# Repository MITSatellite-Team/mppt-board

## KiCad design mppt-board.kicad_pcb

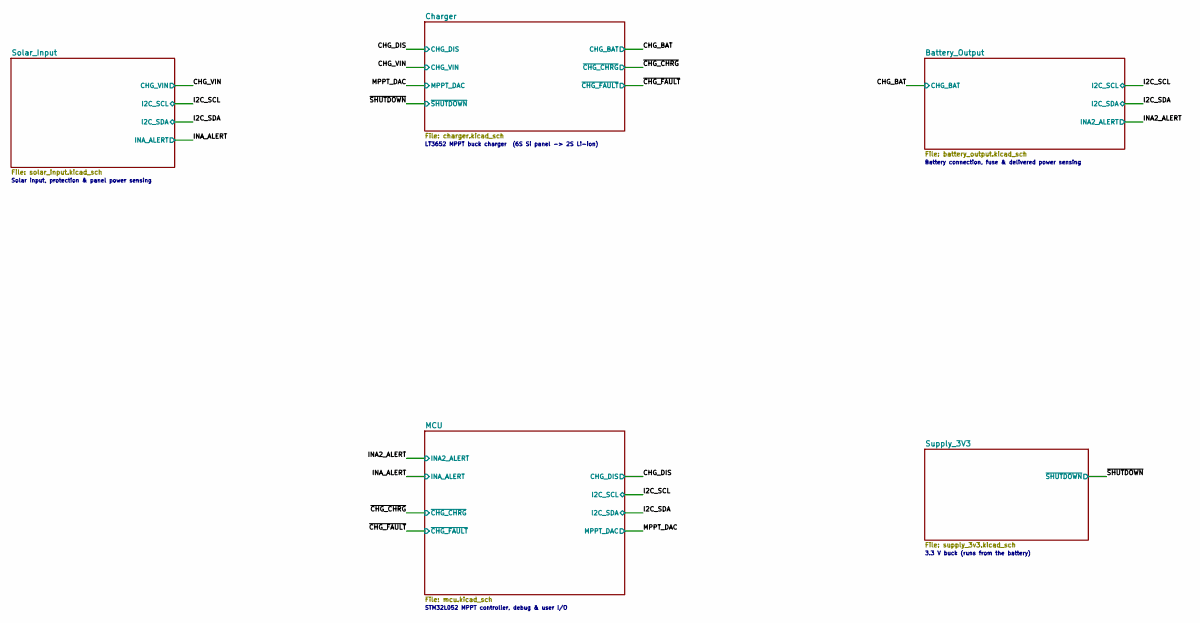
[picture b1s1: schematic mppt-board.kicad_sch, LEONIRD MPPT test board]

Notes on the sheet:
3.3 V buck (runs from the battery)
Solar input, protection & panel power sensing
STM32L052 MPPT controller, debug & user I/O
Battery connection, fuse & delivered power sensing
LT3652 MPPT buck charger (6S Si panel -> 2S Li-ion)

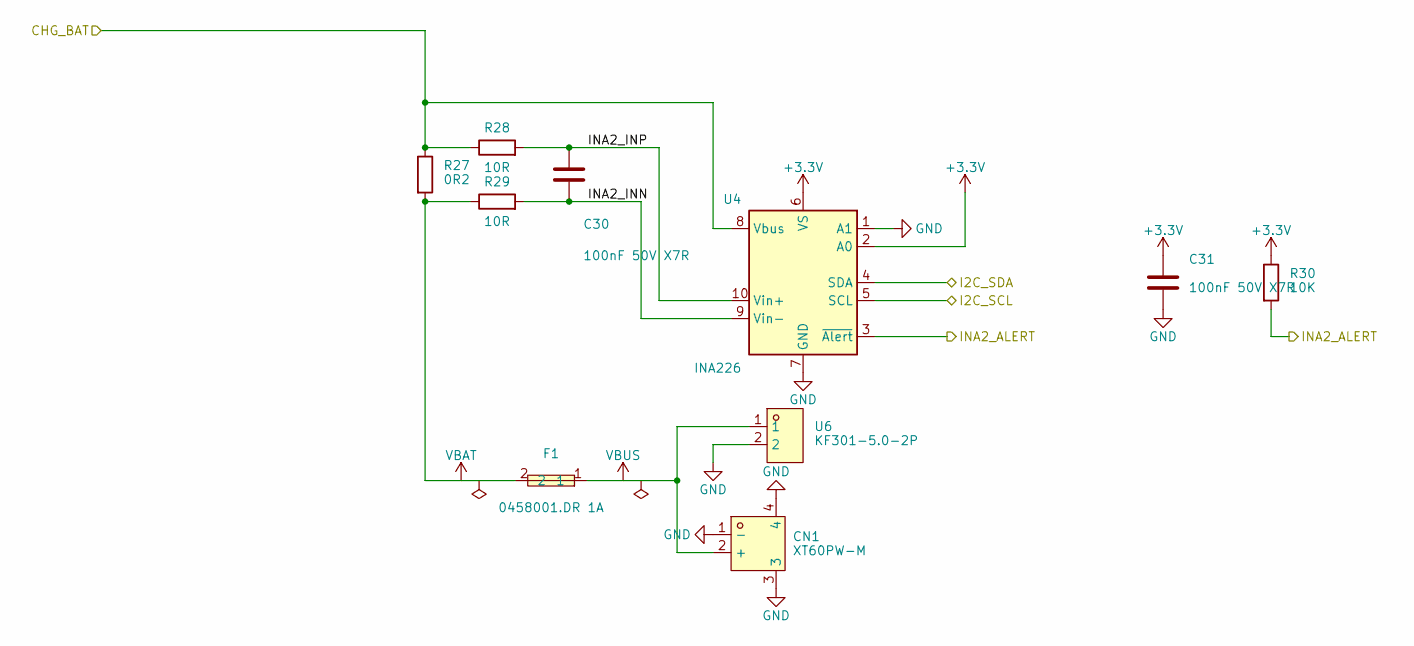
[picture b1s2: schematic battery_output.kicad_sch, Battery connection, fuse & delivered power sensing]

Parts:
C30, C31: 100nF 50V X7R; C_0603_1608Metric; MPN CC0603KRX7R9BB104; LCSC Part C14663
CN1: XT60PW-M; CONN-TH_XT60PW-M; MPN XT60PW-M; LCSC Part C98732
F1: 0458001.DR 1A; Fuse_1206_3216Metric; MPN 0458001.DR; LCSC Part C187559
R27: 0R2; R_1206_3216Metric; MPN RL12FTNR200; LCSC Part C160920
R28, R29: 10R; R_0603_1608Metric; MPN 0603WAF100JT5E; LCSC Part C22859
R30: 10K; R_0603_1608Metric; MPN 0603WAF1002T5E; LCSC Part C25804
U4: INA226; TSSOP-10_3x3mm_P0.5mm; MPN INA226AIDGSR; LCSC Part C49851
U6: KF301-5.0-2P; CONN-TH_P5.00_KF301-5.0-2P; MPN KF301-5.0-2P; LCSC Part C474881

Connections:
+3.3V: C31.1, R30.1, U4.2 (A0), U4.6 (VS); also elsewhere on the board
/Battery_Output/INA2_INN: C30.2, R29.2, U4.9 (Vin-)
/Battery_Output/INA2_INP: C30.1, R28.2, U4.10 (Vin+)
/CHG_BAT: R27.1, R28.1, U4.8 (Vbus); also elsewhere on the board
/I2C_SCL: U4.5 (SCL); also elsewhere on the board
/I2C_SDA: U4.4 (SDA); also elsewhere on the board
/INA2_ALERT: R30.2, U4.3 (~Alert); also elsewhere on the board
GND: C31.2, CN1.1 (-), CN1.3, CN1.4, U4.1 (A1), U4.7 (GND), U6.2; also elsewhere on the board
VBAT: F1.2, R27.2, R29.1; also elsewhere on the board
VBUS: CN1.2 (+), F1.1, U6.1

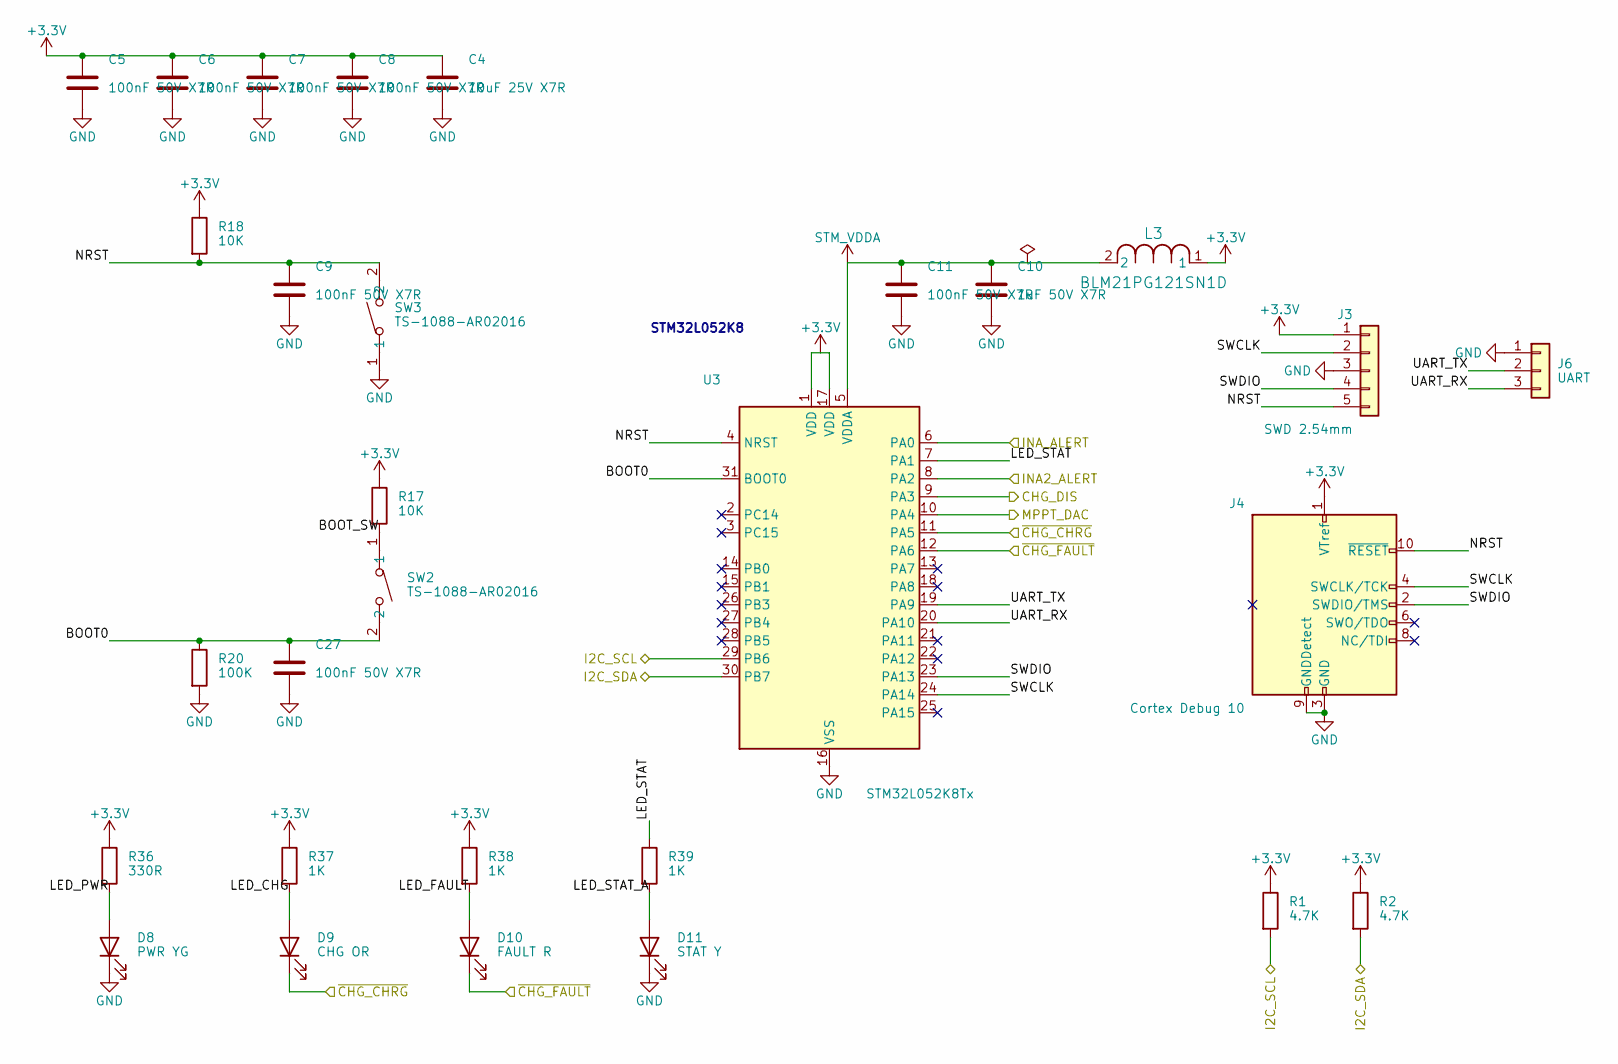
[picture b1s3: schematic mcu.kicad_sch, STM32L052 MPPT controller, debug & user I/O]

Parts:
C4: 10uF 25V X7R; C_0805_2012Metric; MPN CL21B106KAYQNNE; LCSC Part C3039694
C5, C6, C7, C8, C9, C11, C27: 100nF 50V X7R; C_0603_1608Metric; MPN CC0603KRX7R9BB104; LCSC Part C14663
C10: 1uF 50V X7R; C_0603_1608Metric; MPN CC0603KRX7R9BB105; LCSC Part C559769
D8: PWR YG; LED_0603_1608Metric; MPN XL-1608SYGC-06; LCSC Part C965805
D9: CHG OR; LED_0603_1608Metric; MPN XL-1608UOC-06; LCSC Part C965800
D10: FAULT R; LED_0603_1608Metric; MPN XL-1608SURC-06; LCSC Part C965799
D11: STAT Y; LED_0603_1608Metric; MPN XL-1608UYC-06; LCSC Part C965802
J3: SWD 2.54mm; PinHeader_1x05_P2.54mm_Vertical; MPN HX PZ2.54-1x5P ZZ; LCSC Part C32713271
J4: Cortex Debug 10; PinHeader_2x05_P1.27mm_Vertical_SMD; MPN 20021121-00010C4LF; LCSC Part C150517
J6: UART; PinHeader_1x03_P2.54mm_Vertical; MPN HX PZ2.54-1x3P ZZ; LCSC Part C32713269
L3: BLM21PG121SN1D; IND_25_0805_FRT; MPN BLM21PG121SN1D; LCSC Part C79382
R1, R2: 4.7K; R_0603_1608Metric; MPN 0603WAF4701T5E; LCSC Part C23162
R17, R18: 10K; R_0603_1608Metric; MPN 0603WAF1002T5E; LCSC Part C25804
R20: 100K; R_0603_1608Metric; MPN 0603WAF1003T5E; LCSC Part C25803
R36: 330R; R_0603_1608Metric; MPN 0603WAF3300T5E; LCSC Part C23138
R37, R38, R39: 1K; R_0603_1608Metric; MPN 0603WAF1001T5E; LCSC Part C21190
SW2, SW3: TS-1088-AR02016; SW-SMD_L3.9-W3.0-P4.45; MPN TS-1088-AR02016; LCSC Part C720477
U3: STM32L052K8Tx; LQFP-32_7x7mm_P0.8mm; MPN STM32L052K8T6; LCSC Part C222404

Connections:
+3.3V: C4.1, C5.1, C6.1, C7.1, C8.1, J3.1, J4.1 (VTref), L3.1, R1.1, R2.1, R17.1, R18.1, R36.1, R37.1, R38.1, U3.1 (VDD), U3.17 (VDD); also elsewhere on the board
/CHG_DIS: U3.9 (PA3); also elsewhere on the board
/I2C_SCL: R1.2, U3.29 (PB6); also elsewhere on the board
/I2C_SDA: R2.2, U3.30 (PB7); also elsewhere on the board
/INA2_ALERT: U3.8 (PA2); also elsewhere on the board
/INA_ALERT: U3.6 (PA0); also elsewhere on the board
/MCU/BOOT0: C27.1, R20.1, SW2.2, U3.31 (BOOT0)
/MCU/BOOT_SW: R17.2, SW2.1
/MCU/LED_CHG: D9.2 (A), R37.2
/MCU/LED_FAULT: D10.2 (A), R38.2
/MCU/LED_PWR: D8.2 (A), R36.2
/MCU/LED_STAT: R39.1, U3.7 (PA1)
/MCU/LED_STAT_A: D11.2 (A), R39.2
/MCU/NRST: C9.1, J3.5, J4.10 (~RESET), R18.2, SW3.2, U3.4 (NRST)
/MCU/SWCLK: J3.2, J4.4 (SWCLK/TCK), U3.24 (PA14)
/MCU/SWDIO: J3.4, J4.2 (SWDIO/TMS), U3.23 (PA13)
/MCU/UART_RX: J6.3, U3.20 (PA10)
/MCU/UART_TX: J6.2, U3.19 (PA9)
/MPPT_DAC: U3.10 (PA4); also elsewhere on the board
/~CHG_CHRG: D9.1 (K), U3.11 (PA5); also elsewhere on the board
/~CHG_FAULT: D10.1 (K), U3.12 (PA6); also elsewhere on the board
GND: C4.2, C5.2, C6.2, C7.2, C8.2, C9.2, C10.2, C11.2, C27.2, D8.1 (K), D11.1 (K), J3.3, J4.3 (GND), J4.5 (GND), J4.9 (GNDDetect), J6.1, R20.2, SW3.1, U3.16 (VSS), U3.32 (VSS); also elsewhere on the board
STM_VDDA: C10.1, C11.1, L3.2, U3.5 (VDDA)

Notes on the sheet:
STM32L052K8

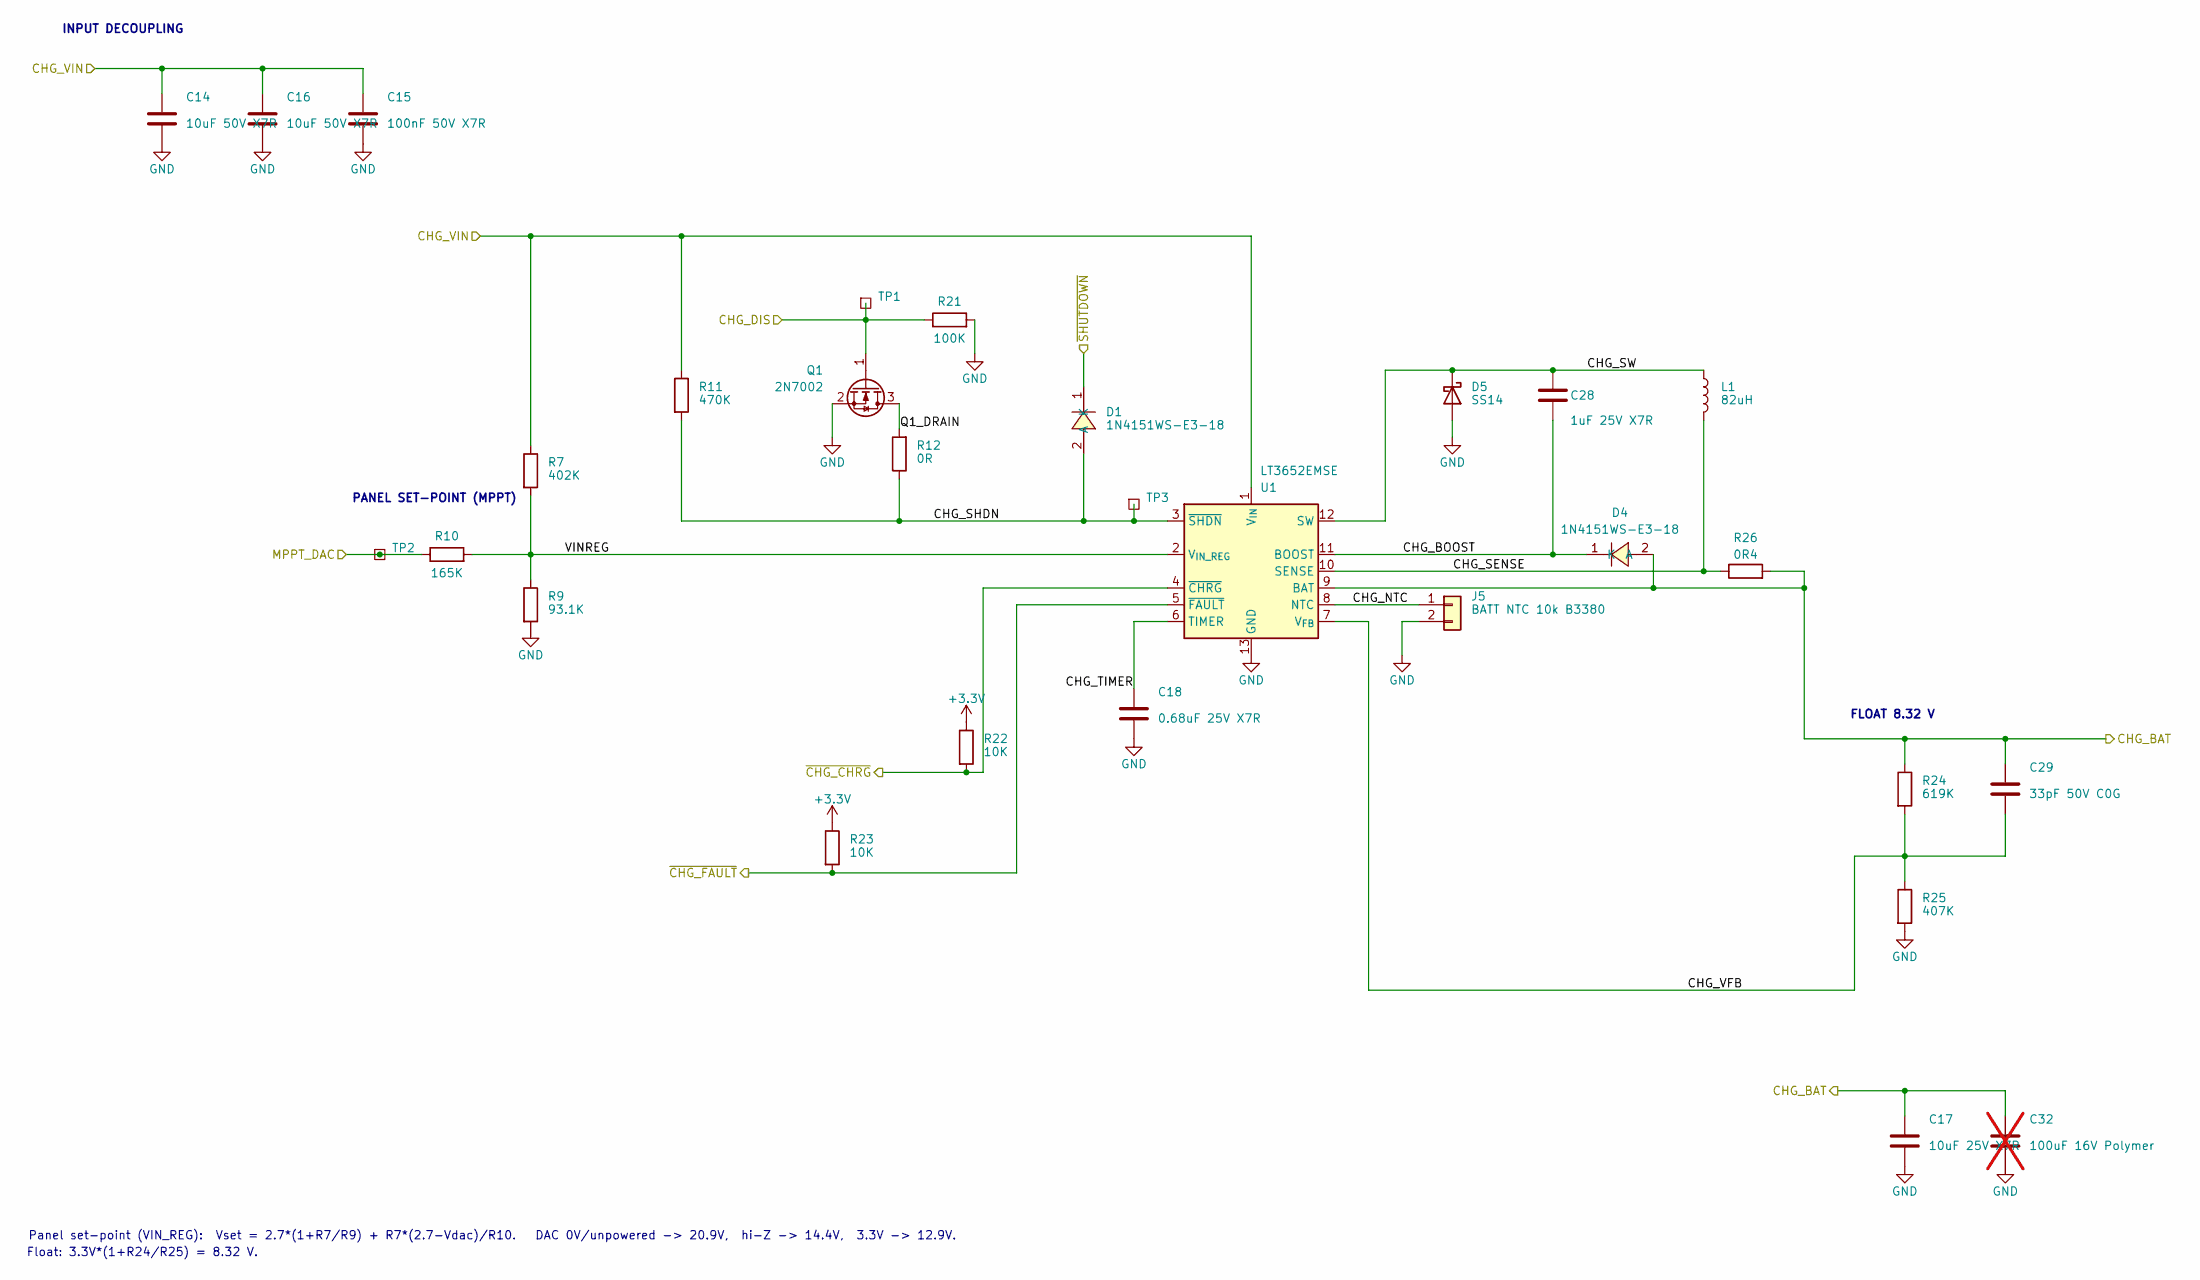
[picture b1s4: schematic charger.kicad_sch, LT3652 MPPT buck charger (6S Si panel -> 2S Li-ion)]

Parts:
C14, C16: 10uF 50V X7R; C_1206_3216Metric; MPN CL31B106KBHNNNE; LCSC Part C89632
C15: 100nF 50V X7R; C_0603_1608Metric; MPN CC0603KRX7R9BB104; LCSC Part C14663
C17: 10uF 25V X7R; C_0805_2012Metric; MPN CL21B106KAYQNNE; LCSC Part C3039694
C18: 0.68uF 25V X7R; C_0603_1608Metric; MPN CC0603KRX7R8BB684; LCSC Part C2838708
C28: 1uF 25V X7R; C_0603_1608Metric; MPN CL10B105KA8NNNC; LCSC Part C29936
C29: 33pF 50V C0G; C_0603_1608Metric; MPN CL10C330JB8NNNC; LCSC Part C1663
C32: 100uF 16V Polymer; CP_EIA-7343-31_Kemet-D; MPN 16TQC100MYF; LCSC Part C109085; not fitted
D1, D4: 1N4151WS-E3-18; SOD-323_L1.8-W1.3-LS2.7-RD; MPN 1N4151WS-E3-18; LCSC Part C17429783
D5: SS14; D_SMA; MPN SS14; LCSC Part C2480
J5: BATT NTC 10k B3380; PinHeader_1x02_P2.54mm_Vertical; MPN HX PZ2.54-1x2P ZZ; LCSC Part C32713268
L1: 82uH; L_Changjiang_FNR6045S; MPN FNR6045S820MT; LCSC Part C168093
Q1: 2N7002; SOT-23; MPN 2N7002; LCSC Part C8545
R7: 402K; R_0603_1608Metric; MPN 0603WAF4023T5E; LCSC Part C23048
R9: 93.1K; R_0603_1608Metric; MPN 0603WAF9312T5E; LCSC Part C23266
R10: 165K; R_0603_1608Metric; MPN 0603WAF1653T5E; LCSC Part C22816
R11: 470K; R_0603_1608Metric; MPN 0603WAF4703T5E; LCSC Part C23178
R12: 0R; R_0603_1608Metric; MPN 0603WAF0000T5E; LCSC Part C21189
R21: 100K; R_0603_1608Metric; MPN 0603WAF1003T5E; LCSC Part C25803
R22, R23: 10K; R_0603_1608Metric; MPN 0603WAF1002T5E; LCSC Part C25804
R24: 619K; R_0603_1608Metric; MPN RT0603BRD07619KL; LCSC Part C861497
R25: 407K; R_0603_1608Metric; MPN RT0603BRD07407KL; LCSC Part C861390
R26: 0R4; R_0805_2012Metric; MPN FRL0805FR400TS; LCSC Part C2934266
TP1: CHG_DIS; TestPoint_Pad_1.5x1.5mm
TP2: MPPT_DAC; TestPoint_Pad_1.5x1.5mm
TP3: CHG_SHDN; TestPoint_Pad_1.5x1.5mm
U1: LT3652EMSE; MSOP-12-1EP_3x4.039mm_P0.65mm_EP1.651x2.845mm_ThermalVias; MPN LT3652EMSE#PBF; LCSC Part C580114

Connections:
+3.3V: R22.1, R23.1; also elsewhere on the board
/CHG_BAT: C17.1, C29.1, C32.1, D4.2 (A), R24.1, R26.2, U1.9 (BAT); also elsewhere on the board
/CHG_DIS: Q1.1 (G), R21.1, TP1.1 (1_1); also elsewhere on the board
/CHG_VIN: C14.1, C15.1, C16.1, R7.1, R11.1, U1.1 (V_{IN}); also elsewhere on the board
/Charger/CHG_BOOST: C28.1, D4.1 (K), U1.11 (BOOST)
/Charger/CHG_NTC: J5.1, U1.8 (NTC)
/Charger/CHG_SENSE: L1.2, R26.1, U1.10 (SENSE)
/Charger/CHG_SHDN: D1.2 (A), R11.2, R12.1, TP3.1 (1_1), U1.3 (~SHDN)
/Charger/CHG_SW: C28.2, D5.1 (K), L1.1, U1.12 (SW)
/Charger/CHG_TIMER: C18.1, U1.6 (TIMER)
/Charger/CHG_VFB: C29.2, R24.2, R25.1, U1.7 (V_{FB})
/Charger/Q1_DRAIN: Q1.3 (D), R12.2
/Charger/VINREG: R7.2, R9.1, R10.2, U1.2 (V_{IN_REG})
/MPPT_DAC: R10.1, TP2.1 (1_1); also elsewhere on the board
/~CHG_CHRG: R22.2, U1.4 (~CHRG); also elsewhere on the board
/~CHG_FAULT: R23.2, U1.5 (~FAULT); also elsewhere on the board
/~SHUTDOWN: D1.1 (K); also elsewhere on the board
GND: C14.2, C15.2, C16.2, C17.2, C18.2, C32.2, D5.2 (A), J5.2, Q1.2 (S), R9.2, R21.2, R25.2, U1.13 (GND); also elsewhere on the board

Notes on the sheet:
PANEL SET-POINT (MPPT)
Panel set-point (VIN_REG): Vset = 2.7*(1+R7/R9) + R7*(2.7-Vdac)/R10. DAC 0V/unpowered -> 20.9V, hi-Z -> 14.4V, 3.3V -> 12.9V.
INPUT DECOUPLING
Float: 3.3V*(1+R24/R25) = 8.32 V.
FLOAT 8.32 V

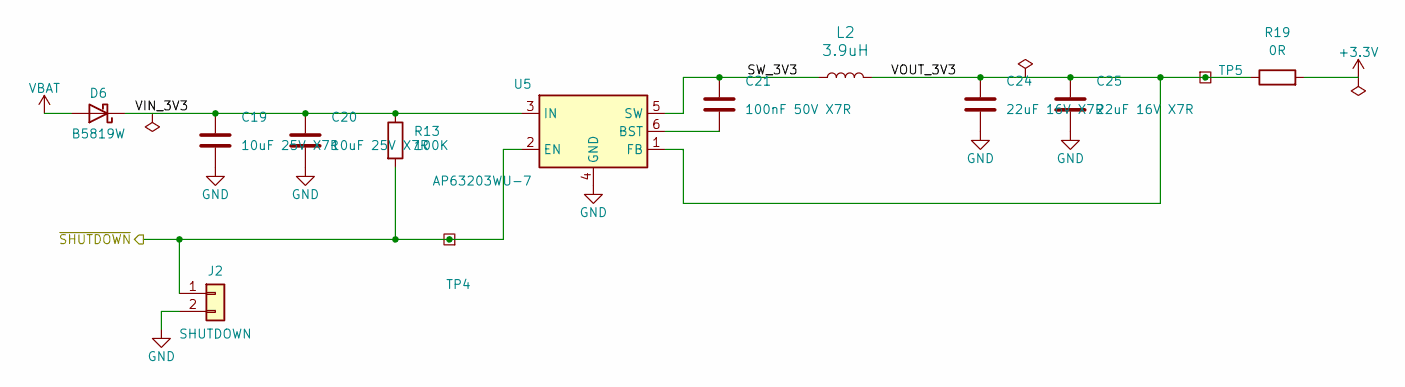
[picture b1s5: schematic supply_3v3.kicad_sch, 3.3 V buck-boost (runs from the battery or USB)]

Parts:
C19, C20: 10uF 25V X7R; C_0805_2012Metric; MPN CL21B106KAYQNNE; LCSC Part C3039694
C21: 100nF 50V X7R; C_0603_1608Metric; MPN CC0603KRX7R9BB104; LCSC Part C14663
C24, C25: 22uF 16V X7R; C_1206_3216Metric; MPN CS3216X7R226K160NRI; LCSC Part C5252682
D6: B5819W; D_SOD-123; MPN B5819W SL; LCSC Part C8598
J2: SHUTDOWN; PinHeader_1x02_P2.54mm_Vertical; MPN HX PZ2.54-1x2P ZZ; LCSC Part C32713268
L2: 3.9uH; L_Sunlord_SWPA4030S; MPN SWPA4030S3R9MT; LCSC Part C96899
R13: 100K; R_0603_1608Metric; MPN 0603WAF1003T5E; LCSC Part C25803
R19: 0R; R_0805_2012Metric; MPN 0805W8F0000T5E; LCSC Part C17477
TP4, TP5: TestPoint_Square; TestPoint_Pad_2.5x2.5mm
U5: AP63203WU-7; TSOT-23-6; MPN AP63203WU-7; LCSC Part C780769

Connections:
+3.3V: R19.2; also elsewhere on the board
/Supply_3V3/SW_3V3: C21.1, L2.1, U5.5 (SW)
/Supply_3V3/VIN_3V3: C19.1, C20.1, D6.1 (K), R13.1, U5.3 (IN)
/Supply_3V3/VOUT_3V3: C24.1, C25.1, L2.2, R19.1, TP5.1 (1_1), U5.1 (FB)
/~SHUTDOWN: J2.1, R13.2, TP4.1 (1_1), U5.2 (EN); also elsewhere on the board
GND: C19.2, C20.2, C24.2, C25.2, J2.2, U5.4 (GND); also elsewhere on the board
unnamed: C21.2, U5.6 (BST)
VBAT: D6.2 (A); also elsewhere on the board

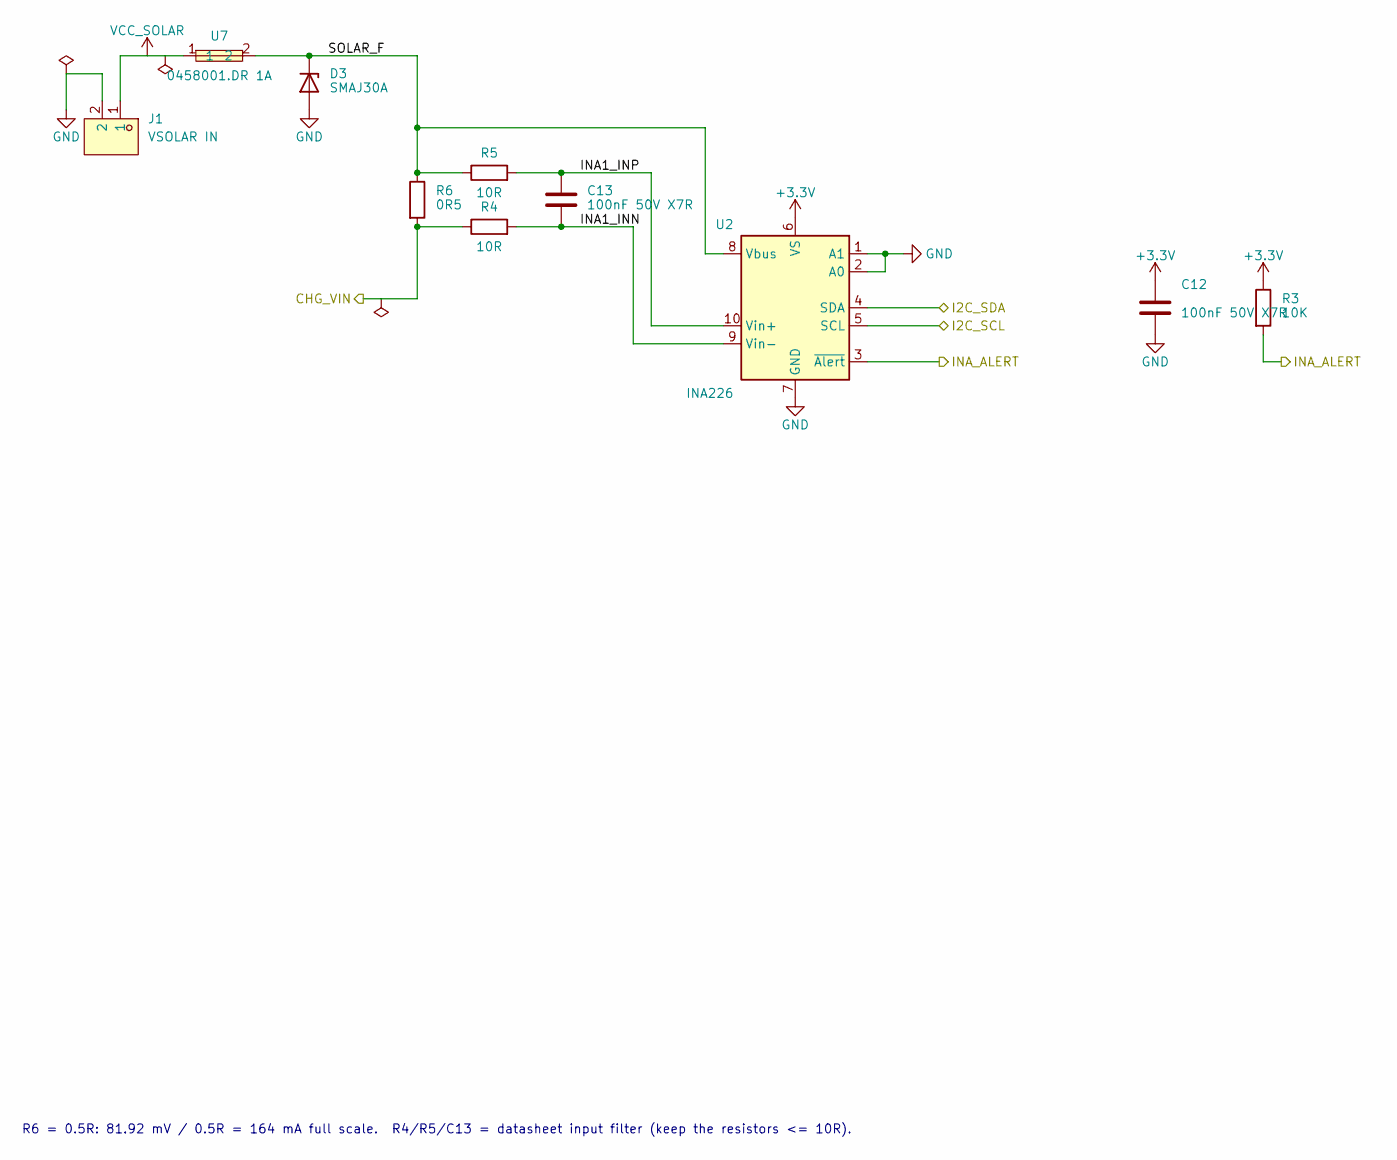
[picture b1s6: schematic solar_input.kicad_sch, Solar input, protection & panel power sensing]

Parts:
C12, C13: 100nF 50V X7R; C_0603_1608Metric; MPN CC0603KRX7R9BB104; LCSC Part C14663
D3: SMAJ30A; D_SMA; MPN SMAJ30A; LCSC Part C148230
J1: VSOLAR IN; CONN-TH_P5.00_KF301-5.0-2P; MPN KF301-5.0-2P; LCSC Part C474881
R3: 10K; R_0603_1608Metric; MPN 0603WAF1002T5E; LCSC Part C25804
R4, R5: 10R; R_0603_1608Metric; MPN 0603WAF100JT5E; LCSC Part C22859
R6: 0R5; R_1206_3216Metric; MPN CSR1206FTR500; LCSC Part C346764
U2: INA226; TSSOP-10_3x3mm_P0.5mm; MPN INA226AIDGSR; LCSC Part C49851
U7: 0458001.DR 1A; Fuse_1206_3216Metric; MPN 0458001.DR; LCSC Part C187559

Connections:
+3.3V: C12.1, R3.1, U2.6 (VS); also elsewhere on the board
/CHG_VIN: R4.1, R6.2; also elsewhere on the board
/I2C_SCL: U2.5 (SCL); also elsewhere on the board
/I2C_SDA: U2.4 (SDA); also elsewhere on the board
/INA_ALERT: R3.2, U2.3 (~Alert); also elsewhere on the board
/Solar_Input/INA1_INN: C13.2, R4.2, U2.9 (Vin-)
/Solar_Input/INA1_INP: C13.1, R5.2, U2.10 (Vin+)
/Solar_Input/SOLAR_F: D3.1 (K), R5.1, R6.1, U2.8 (Vbus), U7.2
GND: C12.2, D3.2 (A), J1.2, U2.1 (A1), U2.2 (A0), U2.7 (GND); also elsewhere on the board
VCC_SOLAR: J1.1, U7.1

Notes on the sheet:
R6 = 0.5R: 81.92 mV / 0.5R = 164 mA full scale. R4/R5/C13 = datasheet input filter (keep the resistors <= 10R).

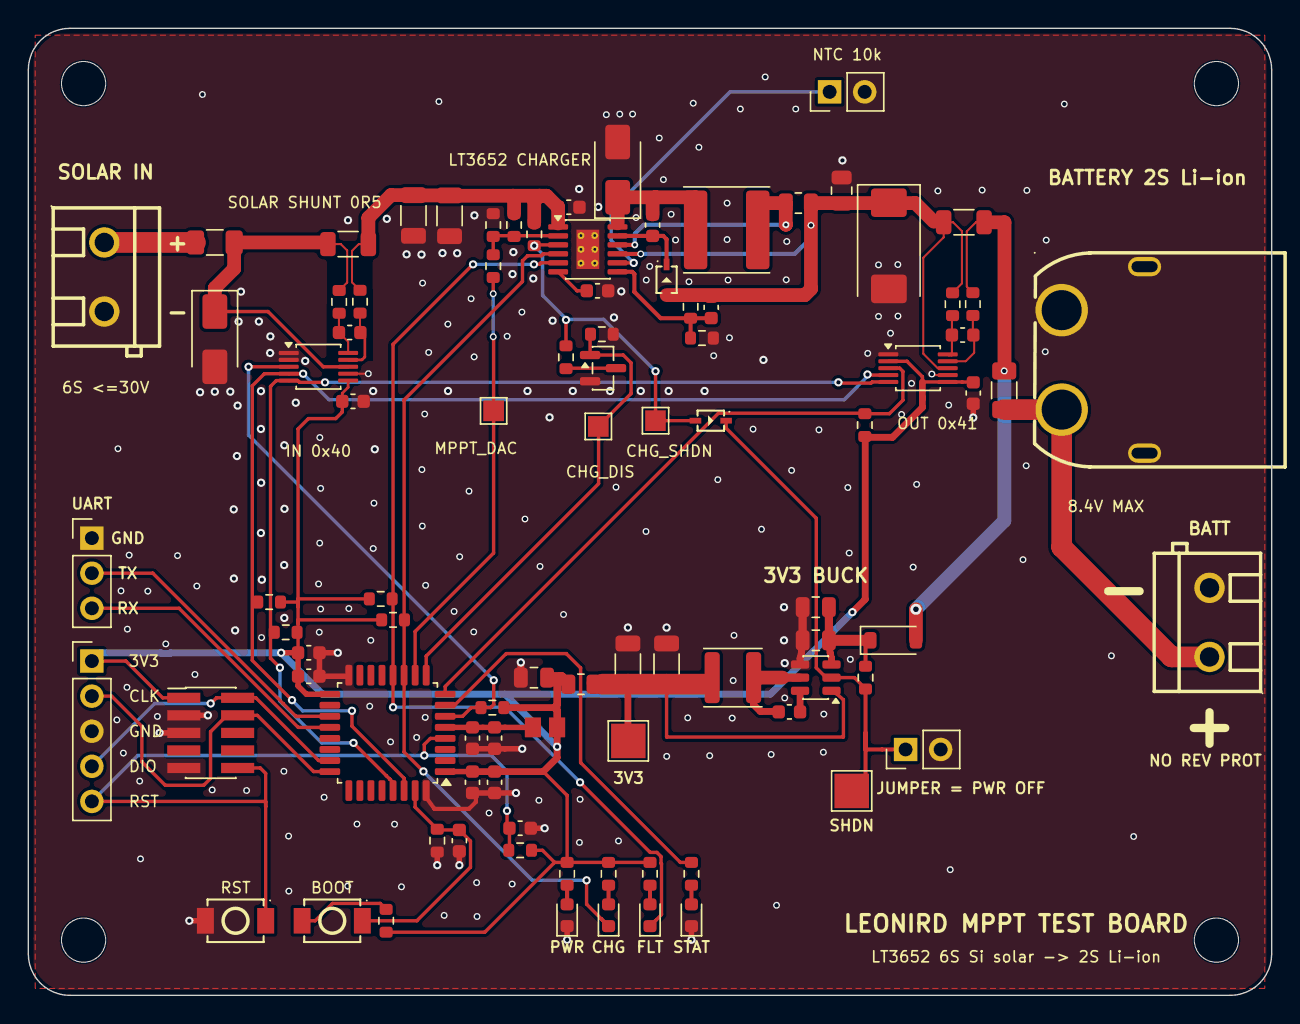
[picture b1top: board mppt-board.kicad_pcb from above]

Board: 4 copper layers, 90.0 x 70.0 mm, 95 parts (0 on the bottom side), 47 nets.

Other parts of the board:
H1, H2, H3, H4: M3; MountingHole_3.2mm_M3
